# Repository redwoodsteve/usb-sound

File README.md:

# usb-sound
USB sound card for ham radio

## Features
 - Adjustable input attenuation (for mic in and left channel)
 - Configurable OMTP jack (TRRS; left, right, mic, gnd)
 - PTT circuit (pulls down to gnd)
 - (Optional) Mini-DIN8 Port compatible with Xiegu transceivers (designed for the G90)
 - CM108B IC

## Technical Details
There is a massive test point (marked "PTT") so you can solder whatever you want to control on.
> [!NOTE]
> The PTT pin is shorted to GND when activated, with no current limiting or decoupling.
There are two audio jacks. By default, they are configured as:
 - OUT: T=Left out, S=GND
 - IN: T=Input, S=GND
The OUT jack is configurable (through two solder jumpers on the back) for an OMTP style:
 - T=Left out
 - R1=Right out
 - R2=Mic in
 - S=GND
There are two 10k potentiometers configured as voltage dividers to attenuate the left channel and the mic input.
They each have a 1k resistor connected from wiper to ground to make them feel more logarithmic.

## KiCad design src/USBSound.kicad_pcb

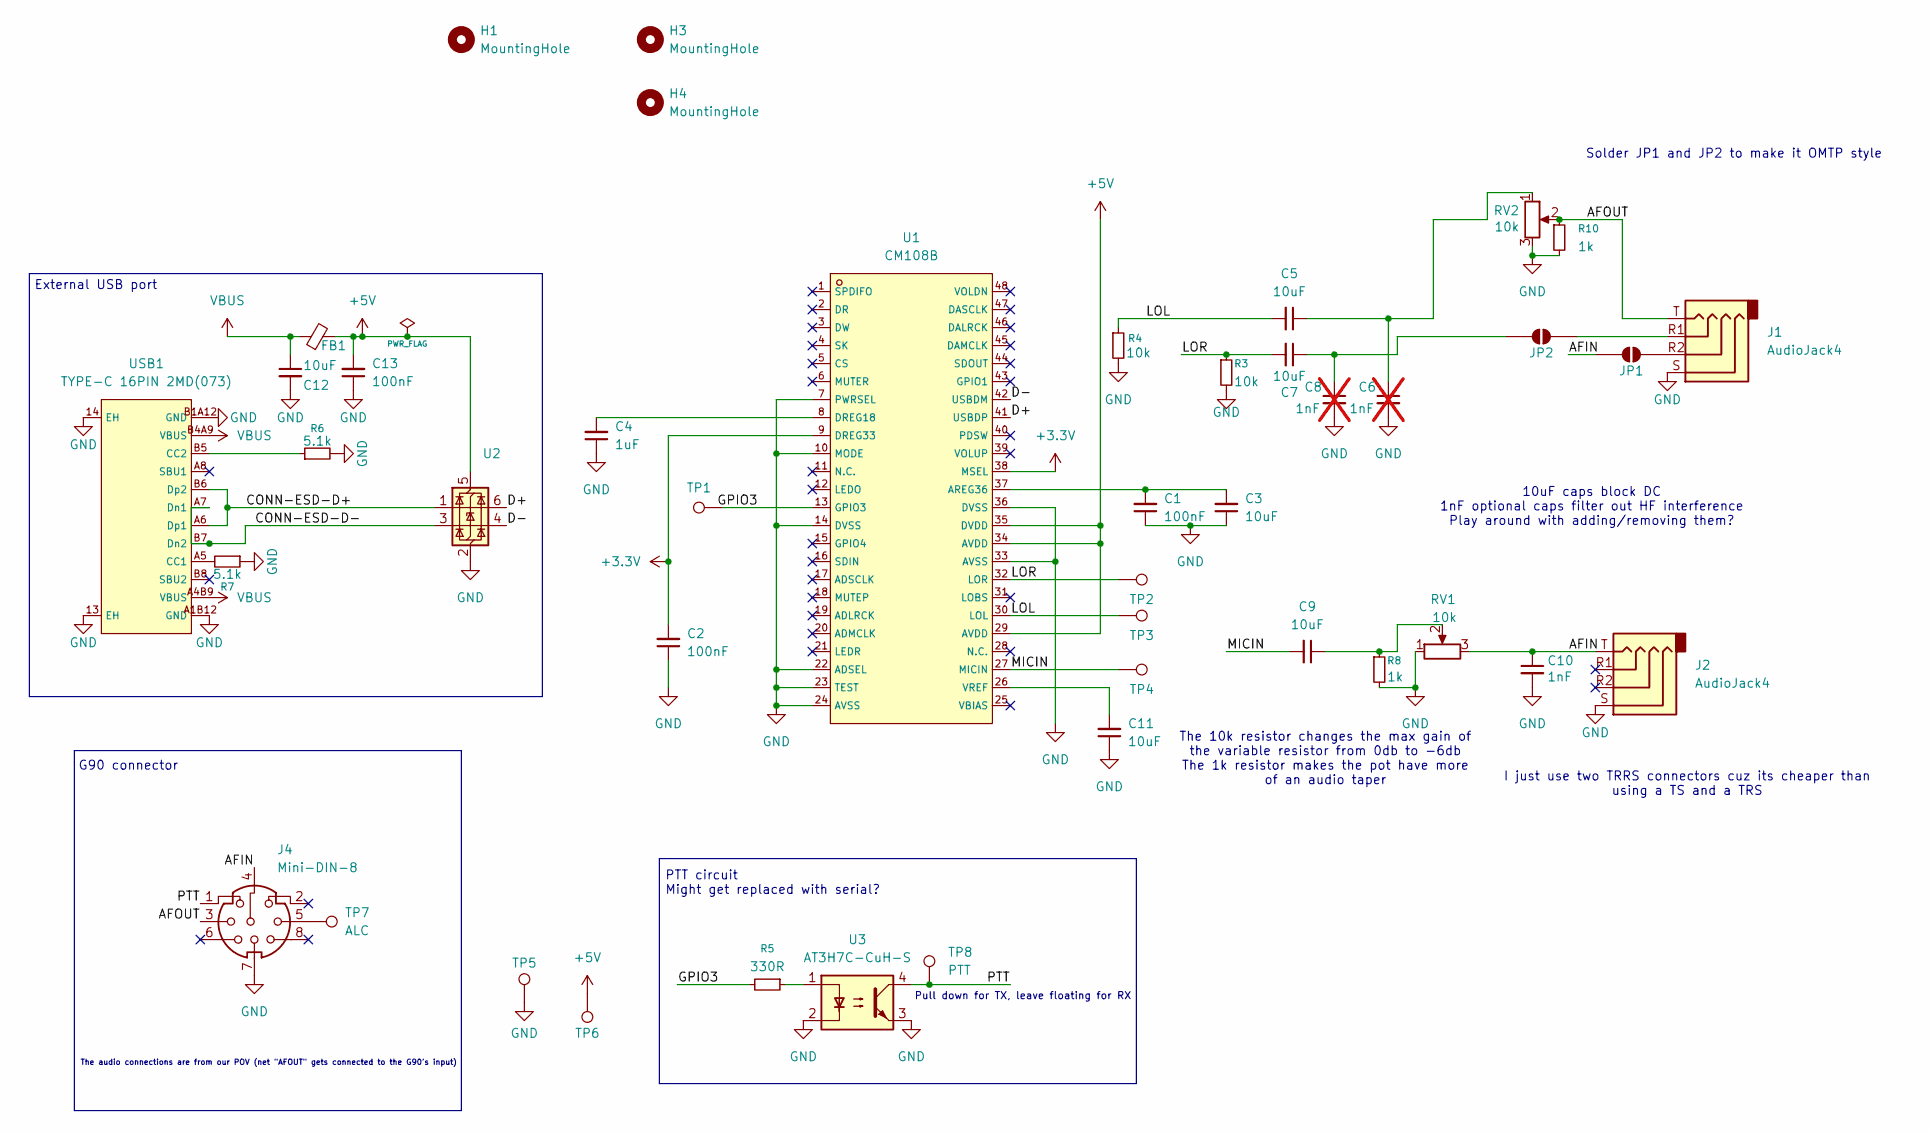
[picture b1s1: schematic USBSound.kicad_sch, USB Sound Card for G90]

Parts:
C1, C2, C13: 100nF; C_0805_2012Metric; LCSC C5137467
C3, C5, C7, C9, C11, C12: 10uF; C_0805_2012Metric; LCSC C1713
C4: 1uF; C_0805_2012Metric; LCSC C28323
C6, C8: 1nF; C_0805_2012Metric; LCSC C94121; not fitted
C10: 1nF; C_0805_2012Metric; LCSC C94121
FB1: MPZ2012S101AT000; C_0805_2012Metric; LCSC C15957
H1, H3, H4: MountingHole; MountingHole_3mm
J1, J2: AudioJack4; Jack_3.5mm_KoreanHropartsElec_PJ-320D-4A_Horizontal; LCSC C95562
J4: Mini-DIN-8; C6456814_CONN-TH_5749267-1-1; LCSC C6456814
JP1, JP2: SolderJumper_2_Open; SolderJumper-2_P1.3mm_Open_RoundedPad1.0x1.5mm
R3, R4: 10k; R_0805_2012Metric; LCSC C2907219
R5: 330R; R_0805_2012Metric; LCSC C2930157
R6, R7: 5.1k; R_0805_2012Metric; LCSC C84375
R8, R10: 1k; R_0805_2012Metric; LCSC C2907219
RV1, RV2: 10k; Potentiometer_Bourns_3296W_Vertical; LCSC C118954
TP1: GPIO3; TestPoint_Pad_D1.5mm
TP2: LOR; TestPoint_Pad_D1.5mm
TP3: LOL; TestPoint_Pad_D1.5mm
TP4: MICIN; TestPoint_Pad_D1.5mm
TP5, TP6: TestPoint; TestPoint_Pad_D1.5mm
TP7: ALC; TestPoint_Pad_D1.5mm
TP8: PTT; TestPoint_Pad_D2.5mm
U1: CM108B; C371347_LQFP-48_L7_0-W7_0-P0_50-LS9_0-BL; LCSC C371347
U2: USBLC6-2SC6; SOT-23-6; LCSC C2827654
U3: AT3H7C-CuH-S; SSOP-4_4.4x2.6mm_P1.27mm; LCSC C20612661
USB1: TYPE-C 16PIN 2MD(073); C2765186_USB-C-SMD_TYPE-C-16PIN-2MD-073; LCSC C2765186

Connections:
+3.3V: C2.2, U1.9 (DREG33), U1.38 (MSEL)
+5V: C13.2, FB1.2, TP6.1 (1_1), U1.29 (AVDD), U1.34 (AVDD), U1.35 (DVDD), U2.5 (VBUS)
/AFIN: C10.1, J2.T, J4.4, JP1.1 (A), RV1.3
/AFOUT: J1.T, J4.3, R10.1, RV2.2
/CONN-ESD-D+: U2.1 (I/O1), USB1.A6 (Dp1), USB1.B6 (Dp2)
/CONN-ESD-D-: U2.3 (I/O2), USB1.A7 (Dn1), USB1.B7 (Dn2)
/D+: U1.41 (USBDP), U2.6 (I/O1)
/D-: U1.42 (USBDM), U2.4 (I/O2)
/GPIO3: R5.2, TP1.1 (1_1), U1.13 (GPIO3)
/LOL: C5.2, R4.1, TP3.1 (1_1), U1.30 (LOL)
/LOR: C7.2, R3.1, TP2.1 (1_1), U1.32 (LOR)
/MICIN: C9.2, TP4.1 (1_1), U1.27 (MICIN)
/PTT: J4.1, TP8.1 (1_1), U3.4
GND: C1.1, C2.1, C3.1, C4.1, C6.2, C8.2, C10.2, C11.1, C12.2, C13.1, J1.S, J2.S, J4.7, R3.2, R4.2, R6.2, R7.1, R8.2, R10.2, RV1.1, RV2.3, TP5.1 (1_1), U1.7 (PWRSEL), U1.10 (MODE), U1.14 (DVSS), U1.22 (ADSEL), U1.23 (TEST), U1.24 (AVSS), U1.33 (AVSS), U1.36 (DVSS), U2.2 (GND), U3.2, U3.3, USB1.13 (EH), USB1.14 (EH), USB1.A1B12 (GND), USB1.B1A12 (GND)
unnamed: C5.1, C6.1, RV2.1
unnamed: C9.1, R8.1, RV1.2
unnamed: J4.5, TP7.1 (1_1)
unnamed: J1.R2, JP1.2 (B)
unnamed: C7.1, C8.1, JP2.1 (A)
unnamed: J1.R1, JP2.2 (B)
unnamed: R5.1, U3.1
unnamed: C1.2, C3.2, U1.37 (AREG36)
unnamed: C4.2, U1.8 (DREG18)
unnamed: C11.2, U1.26 (VREF)
unnamed: R7.2, USB1.A5 (CC1)
unnamed: R6.1, USB1.B5 (CC2)
VBUS: C12.1, FB1.1, USB1.A4B9 (VBUS), USB1.B4A9 (VBUS)

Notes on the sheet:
External USB port
Solder JP1 and JP2 to make it OMTP style
I just use two TRRS connectors cuz its cheaper than using a TS and a TRS
10uF caps block DC 1nF optional caps filter out HF interference Play around with adding/removing them?
G90 connector
PTT circuit Might get replaced with serial?
Pull down for TX, leave floating for RX
The audio connections are from our POV (net "AFOUT" gets connected to the G90's input)
The 10k resistor changes the max gain of the variable resistor from 0db to -6db The 1k resistor makes the pot have more of an audio taper

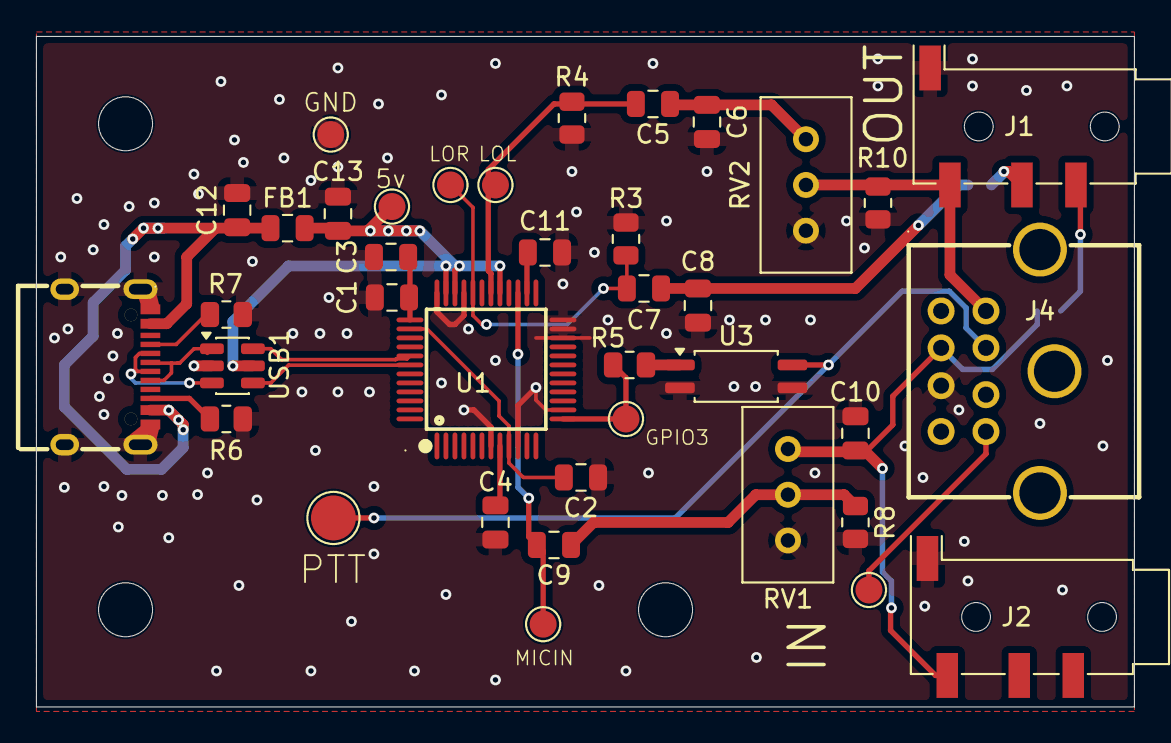
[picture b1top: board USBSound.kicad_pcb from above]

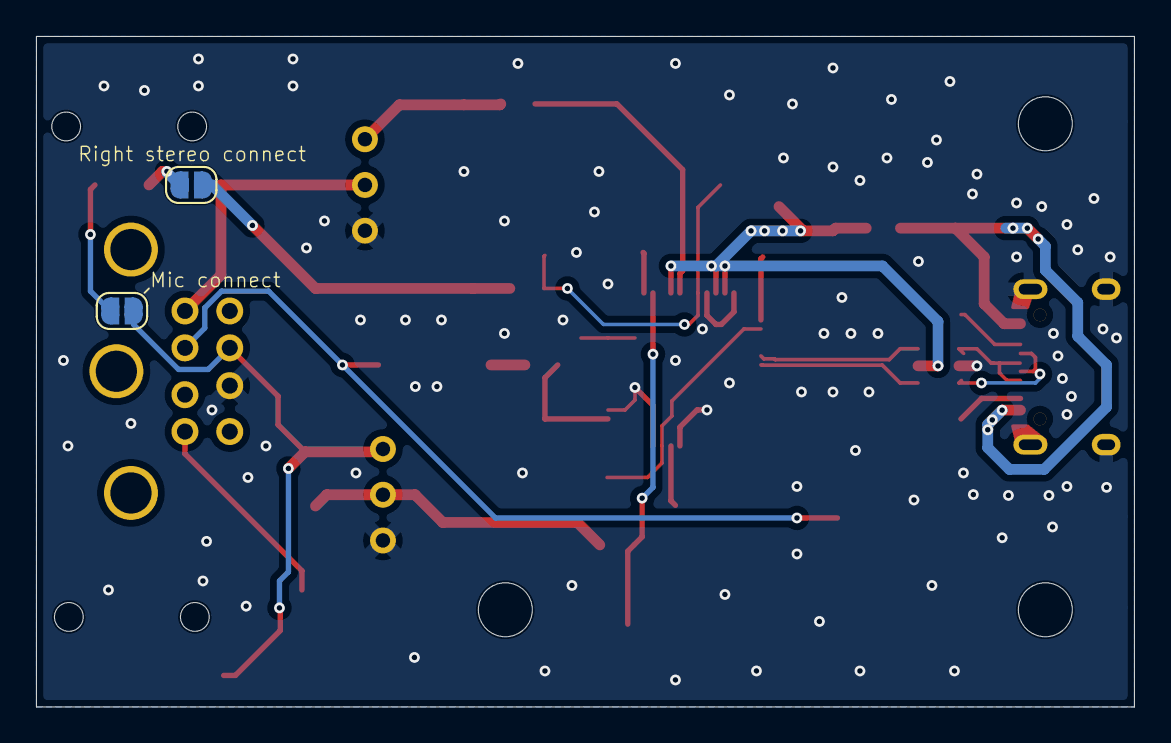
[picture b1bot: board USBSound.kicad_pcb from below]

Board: 2 copper layers, 61.0 x 37.2 mm, 43 parts (2 on the bottom side), 27 nets.
